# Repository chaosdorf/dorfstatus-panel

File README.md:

# moved to Codeberg

This project has been moved to Codeberg: https://codeberg.org/Chaosdorf/dorfstatus-panel

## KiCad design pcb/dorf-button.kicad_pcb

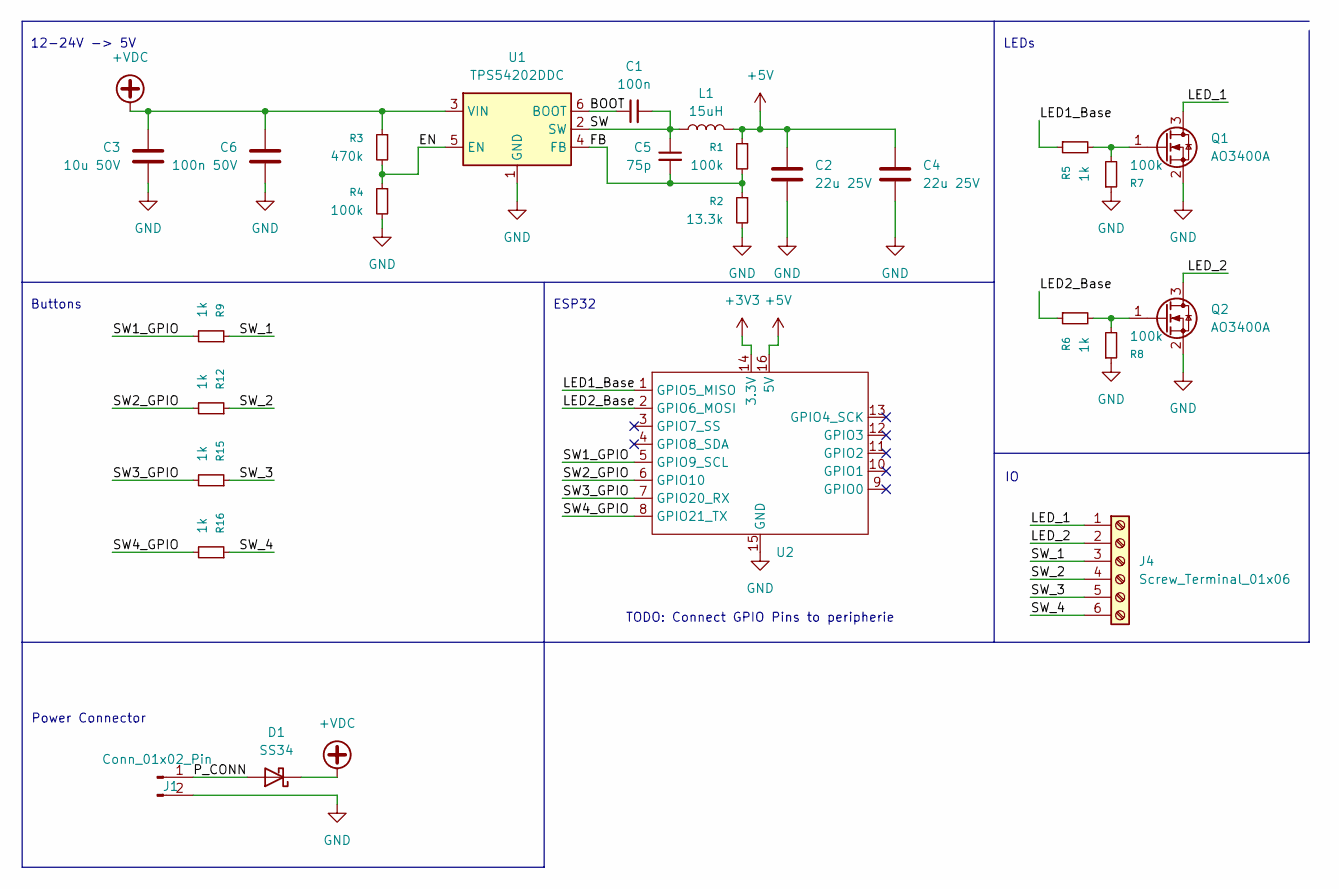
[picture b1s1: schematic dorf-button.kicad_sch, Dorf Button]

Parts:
C1: 100n; C_0603_1608Metric; LCSC C14663
C2, C4: 22u 25V; C_0805_2012Metric
C3: 10u 50V; C_0805_2012Metric
C5: 75p; C_0603_1608Metric; LCSC C14663
C6: 100n 50V; C_0603_1608Metric
D1: SS34; D_SMA
J1: Conn_01x02_Pin; TerminalBlock_Phoenix_MKDS-1,5-2_1x02_P5.00mm_Horizontal
J4: Screw_Terminal_01x06; TerminalBlock_Phoenix_MKDS-1,5-6_1x06_P5.00mm_Horizontal
L1: 15uH; L_APV_ANR4030; LCSC C602033
Q1, Q2: AO3400A; SOT-23
R1, R4, R7, R8: 100k; R_0603_1608Metric
R2: 13.3k; R_0603_1608Metric
R3: 470k; R_0603_1608Metric
R5, R6, R9, R12, R15, R16: 1k; R_0603_1608Metric
U1: TPS54202DDC; SOT-23-6
U2: ESP32-C3_SuperMini

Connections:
+3V3: U2.14 (3.3V)
+5V: C2.1, C4.1, L1.2, R1.1, U2.16 (5V)
+VDC: C3.1, C6.1, D1.1 (K), R3.1, U1.3 (VIN)
/BOOT: C1.1, U1.6 (BOOT)
/EN: R3.2, R4.1, U1.5 (EN)
/FB: C5.2, R1.2, R2.1, U1.4 (FB)
/LED1_Base: R5.1, U2.1 (GPIO5_MISO)
/LED2_Base: R6.1, U2.2 (GPIO6_MOSI)
/LED_1: J4.1, Q1.3 (D)
/LED_2: J4.2, Q2.3 (D)
/P_CONN: D1.2 (A), J1.1
/SW: C1.2, C5.1, L1.1, U1.2 (SW)
/SW1_GPIO: R9.2, U2.5 (GPIO9_SCL)
/SW2_GPIO: R12.2, U2.6 (GPIO10)
/SW3_GPIO: R15.2, U2.7 (GPIO20_RX)
/SW4_GPIO: R16.2, U2.8 (GPIO21_TX)
/SW_1: J4.3, R9.1
/SW_2: J4.4, R12.1
/SW_3: J4.5, R15.1
/SW_4: J4.6, R16.1
GND: C2.2, C3.2, C4.2, C6.2, J1.2, Q1.2 (S), Q2.2 (S), R2.2, R4.2, R7.1, R8.1, U1.1 (GND), U2.15 (GND)
unnamed: Q1.1 (G), R5.2, R7.2
unnamed: Q2.1 (G), R6.2, R8.2

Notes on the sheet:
ESP32
Power Connector
12-24V -> 5V
Buttons
LEDs
TODO: Connect GPIO Pins to peripherie

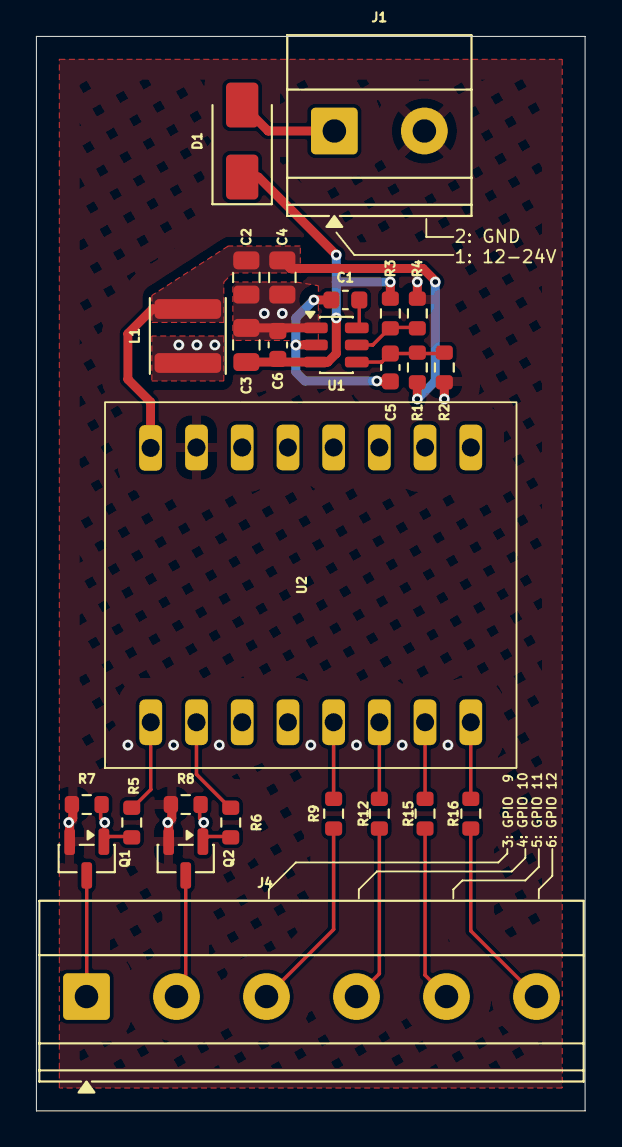
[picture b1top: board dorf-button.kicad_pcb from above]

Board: 4 copper layers, 30.5 x 59.7 mm, 26 parts (0 on the bottom side), 22 nets.

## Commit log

2025-09-03 inital commit
2025-09-03 feat(config): added base ESPHome configuration
2025-09-03 i hate github style markdown line breaks
2025-09-18 fix(docs): clarify power requirements for LEDs
    We did some research and found out that the LEDs are bright enough at at
    least 10V DC. Everything above that is just a bonus, but not needed.
2025-10-07 fix(config): add a domain to the wifi config
    the default .local domain causes problems for us, we can't assign a static IP from our DHCP server.
2025-10-07 feat(config): added the rest of the config :3
2025-10-07 fix(config): check Dorfstatus state before setting it, so it doesn't re-set to the same value
    (because when it re-sets to the same value, it triggers a chat message)
2025-10-07 style(config): move input button descriptions for easier readability
2026-01-02 Add PCB
2026-04-16 moved to Codeberg
